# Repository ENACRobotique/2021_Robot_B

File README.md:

# 2021_Robot_B

Code du robot des 1A du club ENAC Robotique pour la coupe de France de Robotique 2021

## Principe de base du robot:

Le robot est divisé en plusieurs parties:
- Carte Raspberry Pi:

Une carte faisant tourner le système d'exploitation Linux, et donc dotée d'une certaine puissance de calcul.
Elle hébergera le programe AI du projet, qui prendra en charge la gestion des actions, les calculs de déplacement (évitement, pathfinding), ainsi que la communication avec des périphériques de haut-niveau et de bas-niveau (par l'intermédiaire du microcontrolleur).

- Microcontrolleur Teensy:

Une carte disposant de moins de puissance de calcul, mais plus apte à controller les périphériques de bas-niveau tel que les moteurs, servomoteurs, encodeurs, etc.
Cette carte devra exécuter les instructions reçues par voie série envoyées par le RPi, et pourra lui envoyer des messages contenant par exemple des informations de positions calculées d'après les mouvements de roues encodeuses.

- Périphériques de haut-niveau:

Dans cette catégorie est par exemple rangé le LIDAR, qui permet d'obtenir des informations sur les objets se trouvant dans l'envrionnement du robot (autres robots en mouvement par exemple), ou un éventuel capteur de distance à ultrasons (si implémenté). Ils sont controllés directement par le RPi.

- Périphérique de bas-niveau:

Dans cette catégorie sont rangés les moteurs, servomoteurs, encodeurs et autres actionneurs nécessitant d'être controllés précisément. Ils sont controllés par le microcontrolleur.

## Structure Logicielle

En raison de la pandémie de Coronavirus, et du confinement, il ne nous est pas possible de travailler en mélangeant phase de conception et phase pratique. Il est donc nécessaire de pouvoir tester certaines parties du programme qui nécéssite des composants physiques, comme les moteurs, capteurs et autres.

Il a donc été décidé de développer des programmes reproduisant le comportement de ces composants physiques, et permettant de tester des algorithmes s'appuyant sur l'environnement physique du robot.

Schéma représentatif de l'architecture logicielle des différents programmes

### Programmes qui seront embarqués sur le robot (/real/)

- ai :

Le programme qui sera hébergé sur le RPi. Ce programme prendra en charge la gestion des actions, les calculs de déplacement (évitement, pathfinding), l'envoi/réception de messages par la voie série avec le microcontrolleur et controller les périphériques de haut-niveau.

- base :

Le programme sera hébergé sur le microcontrolleur.
Il devra gérer l'envoi/réception de messages par la voie série avec le RPi, et controller les différents périphériques de bas-niveau.

(Les dépendances ne sont pas indiquées ici, merci de vous référer aux README de chaque dossier.)

### Programmes destinés à la simulation (/simu/)

- simu/mym.py:

Ce programme a pour but de reproduire le comportement du microcontrolleur, ainsi que des périphériques de bas-niveau qui y seront connectés. Il est possible d'introduire des erreurs factices afin de tester la robustesse du reste du programme.

- simu/hlm.py:

Ce programme a pour but de reproduire le comportement des périphériques de haut-niveau qui seront connectés au RPi (notamment le LIDAR). Ce programme pourra exploiter les données du NVMU (émulateur d'environnement afin de permettre le test d'algorithmes basés sur l'environnement du robot (comme la détection d'obstacles ou le pathfinding)).

- simu/nvmu.py:

Ce programme a pur but de créer un environnement virtuel qui puisse être exploités par les périhpériques de haut-niveau virtuels, en absence de tests physique. Une fidélité physique complète n'est pas le but recherché, le NVMU ne sera qu'en 2D, le but ne'étant que de pouvoir affiner les algorithmes qui seront utilisés sur le vrai robot.

- simu/emulate_serial_ports.sh:

Un script permettant de mettre en place des canaux de communication série virtuels.

### Programme annexe dédié à la visualisation (/visu/)

- visu/visu.py: (nom hypothétique)

Le but de ce programme est d'offrir aux développeurs un moyen de regarder en temps réel ce que l'AI calcule, et si les résultats sont conformes aux attentes. Le programme pourra accéder aux informations calculées par l'AI, et pourra voir ou modifier le NVMU si il est lancé, afin de voir la réaction du robot.

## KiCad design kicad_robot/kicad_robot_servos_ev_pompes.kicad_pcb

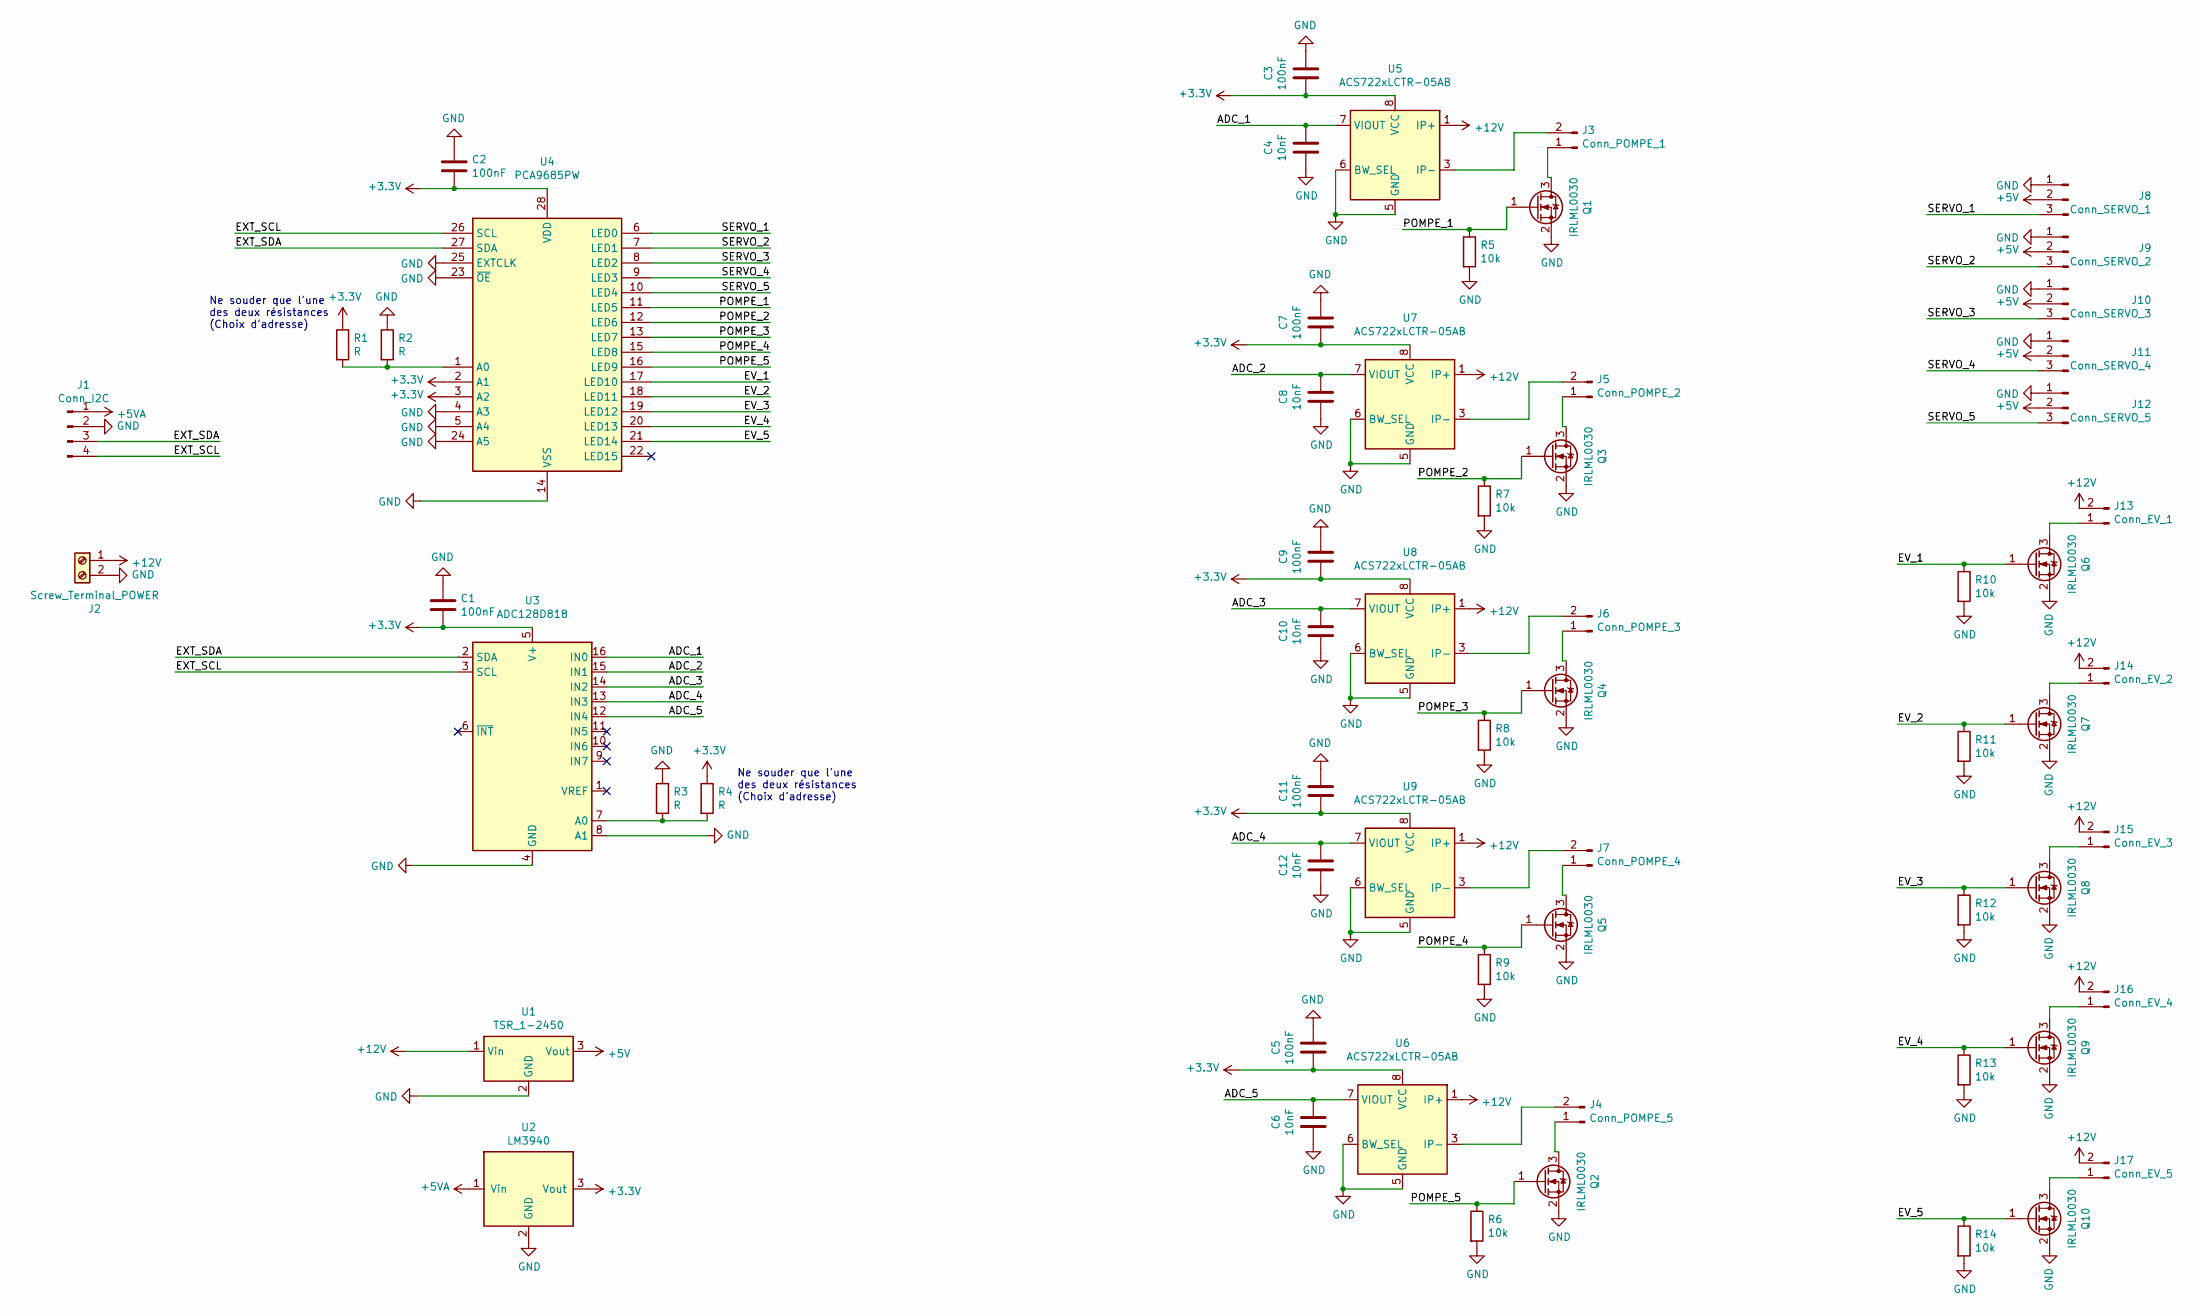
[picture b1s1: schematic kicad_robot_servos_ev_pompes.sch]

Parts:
C1, C2, C3, C5, C7, C9, C11: 100nF; C_0603_1608Metric_Pad1.08x0.95mm_HandSolder
C4, C6, C8, C10, C12: 10nF; C_0603_1608Metric_Pad1.08x0.95mm_HandSolder
J1: Conn_I2C; JST_XH_B4B-XH-A_1x04_P2.50mm_Vertical
J2: Screw_Terminal_POWER; TerminalBlock_bornier-2_P5.08mm
J3: Conn_POMPE_1; JST_XH_B2B-XH-A_1x02_P2.50mm_Vertical
J4: Conn_POMPE_5; JST_XH_B2B-XH-A_1x02_P2.50mm_Vertical
J5: Conn_POMPE_2; JST_XH_B2B-XH-A_1x02_P2.50mm_Vertical
J6: Conn_POMPE_3; JST_XH_B2B-XH-A_1x02_P2.50mm_Vertical
J7: Conn_POMPE_4; JST_XH_B2B-XH-A_1x02_P2.50mm_Vertical
J8: Conn_SERVO_1; PinHeader_1x03_P2.54mm_Vertical
J9: Conn_SERVO_2; PinHeader_1x03_P2.54mm_Vertical
J10: Conn_SERVO_3; PinHeader_1x03_P2.54mm_Vertical
J11: Conn_SERVO_4; PinHeader_1x03_P2.54mm_Vertical
J12: Conn_SERVO_5; PinHeader_1x03_P2.54mm_Vertical
J13: Conn_EV_1; JST_XH_B2B-XH-A_1x02_P2.50mm_Vertical
J14: Conn_EV_2; JST_XH_B2B-XH-A_1x02_P2.50mm_Vertical
J15: Conn_EV_3; JST_XH_B2B-XH-A_1x02_P2.50mm_Vertical
J16: Conn_EV_4; JST_XH_B2B-XH-A_1x02_P2.50mm_Vertical
J17: Conn_EV_5; JST_XH_B2B-XH-A_1x02_P2.50mm_Vertical
Q1, Q2, Q3, Q4, Q5, Q6, Q7, Q8, Q9, Q10: IRLML0030; SOT-23
R1, R2, R3, R4: R; R_0603_1608Metric_Pad0.98x0.95mm_HandSolder
R5, R6, R7, R8, R9, R10, R11, R12, R13, R14: 10k; R_0603_1608Metric_Pad0.98x0.95mm_HandSolder
U1: TSR_1-2450; Converter_DCDC_TRACO_TSR-1_THT
U2: LM3940; SOT-223-3_TabPin2
U3: ADC128D818; TSSOP-16_4.4x5mm_P0.65mm
U4: PCA9685PW; TSSOP-28_4.4x9.7mm_P0.65mm
U5, U6, U7, U8, U9: ACS722xLCTR-05AB; SOIC-8_3.9x4.9mm_P1.27mm

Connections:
+3V3: C1.2, C2.2, C3.2, C5.2, C7.2, C9.2, C11.2, R1.1, R4.1, U2.3 (Vout), U3.5 (V+), U4.2 (A1), U4.3 (A2), U4.28 (VDD), U5.8 (VCC), U6.8 (VCC), U7.8 (VCC), U8.8 (VCC), U9.8 (VCC)
+5V: J8.2, J9.2, J10.2, J11.2, J12.2, U1.3 (Vout)
+5VA: J1.1, U2.1 (Vin)
+12V: J2.1, J13.2, J14.2, J15.2, J16.2, J17.2, U1.1 (Vin), U5.1 (IP+), U5.2 (IP+), U6.1 (IP+), U6.2 (IP+), U7.1 (IP+), U7.2 (IP+), U8.1 (IP+), U8.2 (IP+), U9.1 (IP+), U9.2 (IP+)
/ADC_1: C4.1, U3.16 (IN0), U5.7 (VIOUT)
/ADC_2: C8.1, U3.15 (IN1), U7.7 (VIOUT)
/ADC_3: C10.1, U3.14 (IN2), U8.7 (VIOUT)
/ADC_4: C12.1, U3.13 (IN3), U9.7 (VIOUT)
/ADC_5: C6.1, U3.12 (IN4), U6.7 (VIOUT)
/EV_1: Q6.1 (G), R10.1, U4.17 (LED10)
/EV_2: Q7.1 (G), R11.1, U4.18 (LED11)
/EV_3: Q8.1 (G), R12.1, U4.19 (LED12)
/EV_4: Q9.1 (G), R13.1, U4.20 (LED13)
/EV_5: Q10.1 (G), R14.1, U4.21 (LED14)
/EXT_SCL: J1.4, U3.3 (SCL), U4.26 (SCL)
/EXT_SDA: J1.3, U3.2 (SDA), U4.27 (SDA)
/POMPE_1: Q1.1 (G), R5.1, U4.11 (LED5)
/POMPE_2: Q3.1 (G), R7.1, U4.12 (LED6)
/POMPE_3: Q4.1 (G), R8.1, U4.13 (LED7)
/POMPE_4: Q5.1 (G), R9.1, U4.15 (LED8)
/POMPE_5: Q2.1 (G), R6.1, U4.16 (LED9)
/SERVO_1: J8.3, U4.6 (LED0)
/SERVO_2: J9.3, U4.7 (LED1)
/SERVO_3: J10.3, U4.8 (LED2)
/SERVO_4: J11.3, U4.9 (LED3)
/SERVO_5: J12.3, U4.10 (LED4)
GND: C1.1, C2.1, C3.1, C4.2, C5.1, C6.2, C7.1, C8.2, C9.1, C10.2, C11.1, C12.2, J1.2, J2.2, J8.1, J9.1, J10.1, J11.1, J12.1, Q1.2 (S), Q2.2 (S), Q3.2 (S), Q4.2 (S), Q5.2 (S), Q6.2 (S), Q7.2 (S), Q8.2 (S), Q9.2 (S), Q10.2 (S), R2.1, R3.1, R5.2, R6.2, R7.2, R8.2, R9.2, R10.2, R11.2, R12.2, R13.2, R14.2, U1.2 (GND), U2.2 (GND), U3.4 (GND), U3.8 (A1), U4.4 (A3), U4.5 (A4), U4.14 (VSS), U4.23 (~OE), U4.24 (A5), U4.25 (EXTCLK), U5.5 (GND), U5.6 (BW_SEL), U6.5 (GND), U6.6 (BW_SEL), U7.5 (GND), U7.6 (BW_SEL), U8.5 (GND), U8.6 (BW_SEL), U9.5 (GND), U9.6 (BW_SEL)
unnamed: J3.1, Q1.3 (D)
unnamed: J3.2, U5.3 (IP-), U5.4 (IP-)
unnamed: J4.1, Q2.3 (D)
unnamed: J4.2, U6.3 (IP-), U6.4 (IP-)
unnamed: J5.1, Q3.3 (D)
unnamed: J5.2, U7.3 (IP-), U7.4 (IP-)
unnamed: J6.1, Q4.3 (D)
unnamed: J6.2, U8.3 (IP-), U8.4 (IP-)
unnamed: J7.1, Q5.3 (D)
unnamed: J7.2, U9.3 (IP-), U9.4 (IP-)
unnamed: J13.1, Q6.3 (D)
unnamed: J14.1, Q7.3 (D)
unnamed: J15.1, Q8.3 (D)
unnamed: J16.1, Q9.3 (D)
unnamed: J17.1, Q10.3 (D)
unnamed: R1.2, R2.2, U4.1 (A0)
unnamed: R3.2, R4.2, U3.7 (A0)

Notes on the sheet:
Ne souder que l'une des deux résistances (Choix d'adresse)

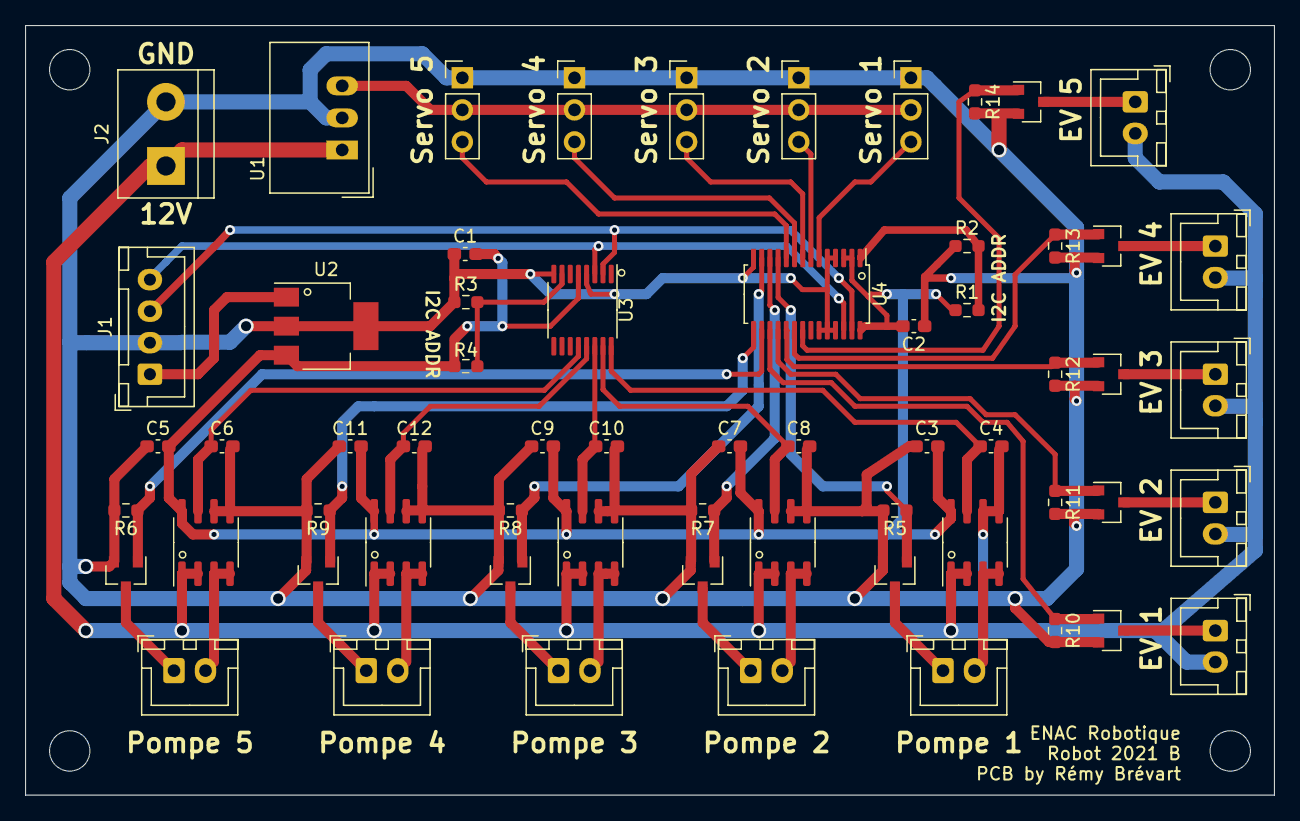
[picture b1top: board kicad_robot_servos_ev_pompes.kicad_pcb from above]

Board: 2 copper layers, 99.0 x 61.0 mm, 62 parts (0 on the bottom side), 44 nets.

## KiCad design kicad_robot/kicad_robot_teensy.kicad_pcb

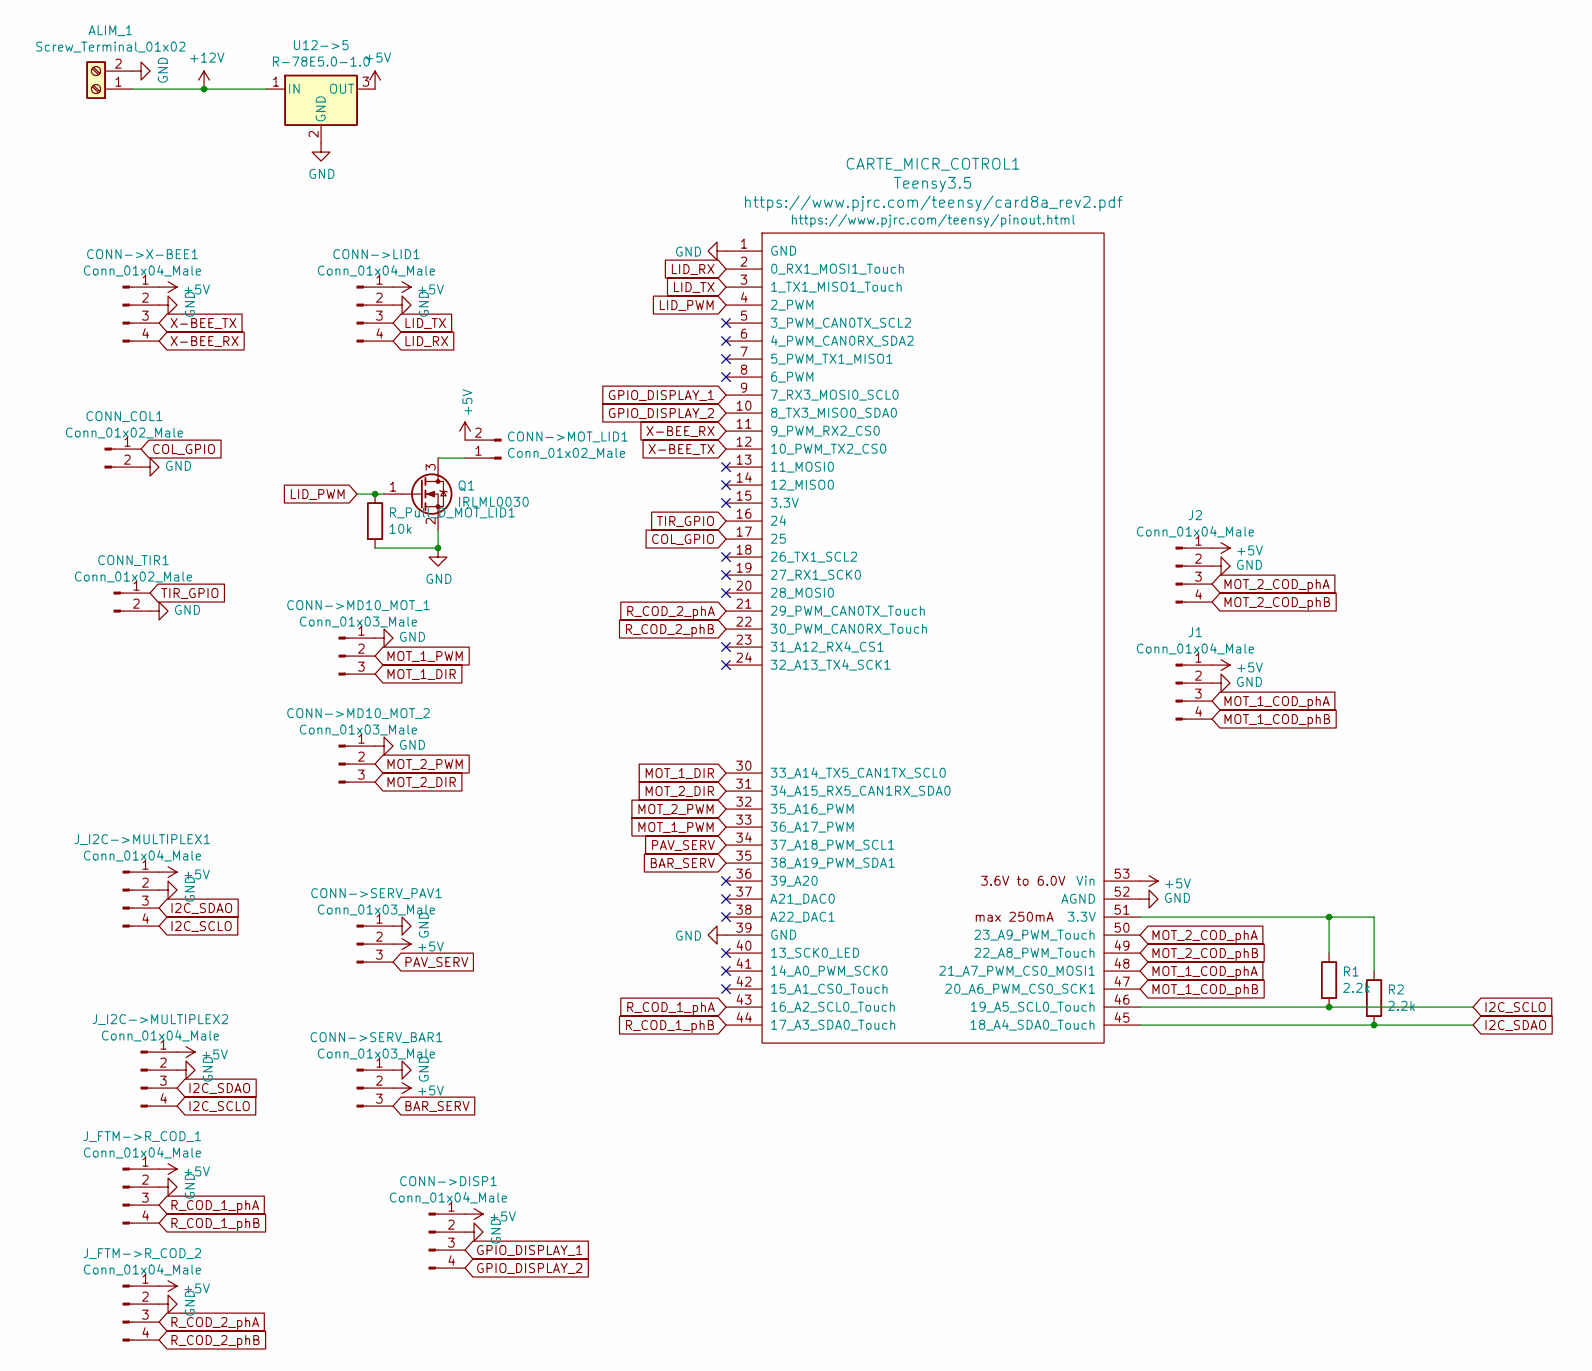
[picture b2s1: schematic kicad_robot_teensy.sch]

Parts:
ALIM_1: Screw_Terminal_01x02; TerminalBlock_bornier-2_P5.08mm
CARTE_MICR_COTROL1: Teensy3.5; Teensy35_36
CONN->DISP1: Conn_01x04_Male; JST_XH_B4B-XH-A_1x04_P2.50mm_Vertical
CONN->LID1: Conn_01x04_Male; JST_XH_B4B-XH-A_1x04_P2.50mm_Vertical
CONN->MD10_MOT_1, CONN->MD10_MOT_2: Conn_01x03_Male; JST_XH_B3B-XH-A_1x03_P2.50mm_Vertical
CONN->MOT_LID1: Conn_01x02_Male; JST_XH_B2B-XH-A_1x02_P2.50mm_Vertical
CONN->SERV_BAR1: Conn_01x03_Male; PinHeader_1x03_P2.54mm_Vertical
CONN->SERV_PAV1: Conn_01x03_Male; PinHeader_1x03_P2.54mm_Vertical
CONN->X-BEE1: Conn_01x04_Male; JST_XH_B4B-XH-A_1x04_P2.50mm_Vertical
CONN_COL1: Conn_01x02_Male; JST_XH_B2B-XH-A_1x02_P2.50mm_Vertical
CONN_TIR1: Conn_01x02_Male; JST_XH_B2B-XH-A_1x02_P2.50mm_Vertical
J1, J2: Conn_01x04_Male
J_FTM->R_COD_1, J_FTM->R_COD_2: Conn_01x04_Male; JST_XH_B4B-XH-A_1x04_P2.50mm_Vertical
J_I2C->MULTIPLEX1, J_I2C->MULTIPLEX2: Conn_01x04_Male; JST_XH_B4B-XH-A_1x04_P2.50mm_Vertical
Q1: IRLML0030; SOT-23
R1, R2: 2.2k; R_0603_1608Metric_Pad0.98x0.95mm_HandSolder
R_Pull_D_MOT_LID1: 10k; R_0603_1608Metric_Pad0.98x0.95mm_HandSolder
U12->5: R-78E5.0-1.0; Converter_DCDC_RECOM_R-78E-0.5_THT

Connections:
+5V: CARTE_MICR_COTROL1.53 (Vin), CONN->DISP1.1, CONN->LID1.1, CONN->MOT_LID1.2, CONN->SERV_BAR1.2, CONN->SERV_PAV1.2, CONN->X-BEE1.1, J1.1, J2.1, J_FTM->R_COD_1.1, J_FTM->R_COD_2.1, J_I2C->MULTIPLEX1.1, J_I2C->MULTIPLEX2.1, U12->5.3 (OUT)
+12V: ALIM_1.1, U12->5.1 (IN)
BAR_SERV: CARTE_MICR_COTROL1.35 (38_A19_PWM_SDA1), CONN->SERV_BAR1.3
COL_GPIO: CARTE_MICR_COTROL1.17 (25), CONN_COL1.1
GND: ALIM_1.2, CARTE_MICR_COTROL1.1 (GND), CARTE_MICR_COTROL1.39 (GND), CARTE_MICR_COTROL1.52 (AGND), CONN->DISP1.2, CONN->LID1.2, CONN->MD10_MOT_1.1, CONN->MD10_MOT_2.1, CONN->SERV_BAR1.1, CONN->SERV_PAV1.1, CONN->X-BEE1.2, CONN_COL1.2, CONN_TIR1.2, J1.2, J2.2, J_FTM->R_COD_1.2, J_FTM->R_COD_2.2, J_I2C->MULTIPLEX1.2, J_I2C->MULTIPLEX2.2, Q1.2 (S), R_Pull_D_MOT_LID1.2, U12->5.2 (GND)
GPIO_DISPLAY_1: CARTE_MICR_COTROL1.9 (7_RX3_MOSI0_SCL0), CONN->DISP1.3
GPIO_DISPLAY_2: CARTE_MICR_COTROL1.10 (8_TX3_MISO0_SDA0), CONN->DISP1.4
I2C_SCLO: CARTE_MICR_COTROL1.46 (19_A5_SCL0_Touch), J_I2C->MULTIPLEX1.4, J_I2C->MULTIPLEX2.4, R1.2
I2C_SDAO: CARTE_MICR_COTROL1.45 (18_A4_SDA0_Touch), J_I2C->MULTIPLEX1.3, J_I2C->MULTIPLEX2.3, R2.2
LID_PWM: CARTE_MICR_COTROL1.4 (2_PWM), Q1.1 (G), R_Pull_D_MOT_LID1.1
LID_RX: CARTE_MICR_COTROL1.2 (0_RX1_MOSI1_Touch), CONN->LID1.4
LID_TX: CARTE_MICR_COTROL1.3 (1_TX1_MISO1_Touch), CONN->LID1.3
MOT_1_COD_phA: CARTE_MICR_COTROL1.48 (21_A7_PWM_CS0_MOSI1), J1.3
MOT_1_COD_phB: CARTE_MICR_COTROL1.47 (20_A6_PWM_CS0_SCK1), J1.4
MOT_1_DIR: CARTE_MICR_COTROL1.30 (33_A14_TX5_CAN1TX_SCL0), CONN->MD10_MOT_1.3
MOT_1_PWM: CARTE_MICR_COTROL1.33 (36_A17_PWM), CONN->MD10_MOT_1.2
MOT_2_COD_phA: CARTE_MICR_COTROL1.50 (23_A9_PWM_Touch), J2.3
MOT_2_COD_phB: CARTE_MICR_COTROL1.49 (22_A8_PWM_Touch), J2.4
MOT_2_DIR: CARTE_MICR_COTROL1.31 (34_A15_RX5_CAN1RX_SDA0), CONN->MD10_MOT_2.3
MOT_2_PWM: CARTE_MICR_COTROL1.32 (35_A16_PWM), CONN->MD10_MOT_2.2
unnamed: CARTE_MICR_COTROL1.51 (3.3V), R1.1, R2.1
unnamed: CONN->MOT_LID1.1, Q1.3 (D)
PAV_SERV: CARTE_MICR_COTROL1.34 (37_A18_PWM_SCL1), CONN->SERV_PAV1.3
R_COD_1_phA: CARTE_MICR_COTROL1.43 (16_A2_SCL0_Touch), J_FTM->R_COD_1.3
R_COD_1_phB: CARTE_MICR_COTROL1.44 (17_A3_SDA0_Touch), J_FTM->R_COD_1.4
R_COD_2_phA: CARTE_MICR_COTROL1.21 (29_PWM_CAN0TX_Touch), J_FTM->R_COD_2.3
R_COD_2_phB: CARTE_MICR_COTROL1.22 (30_PWM_CAN0RX_Touch), J_FTM->R_COD_2.4
TIR_GPIO: CARTE_MICR_COTROL1.16 (24), CONN_TIR1.1
X-BEE_RX: CARTE_MICR_COTROL1.11 (9_PWM_RX2_CS0), CONN->X-BEE1.4
X-BEE_TX: CARTE_MICR_COTROL1.12 (10_PWM_TX2_CS0), CONN->X-BEE1.3

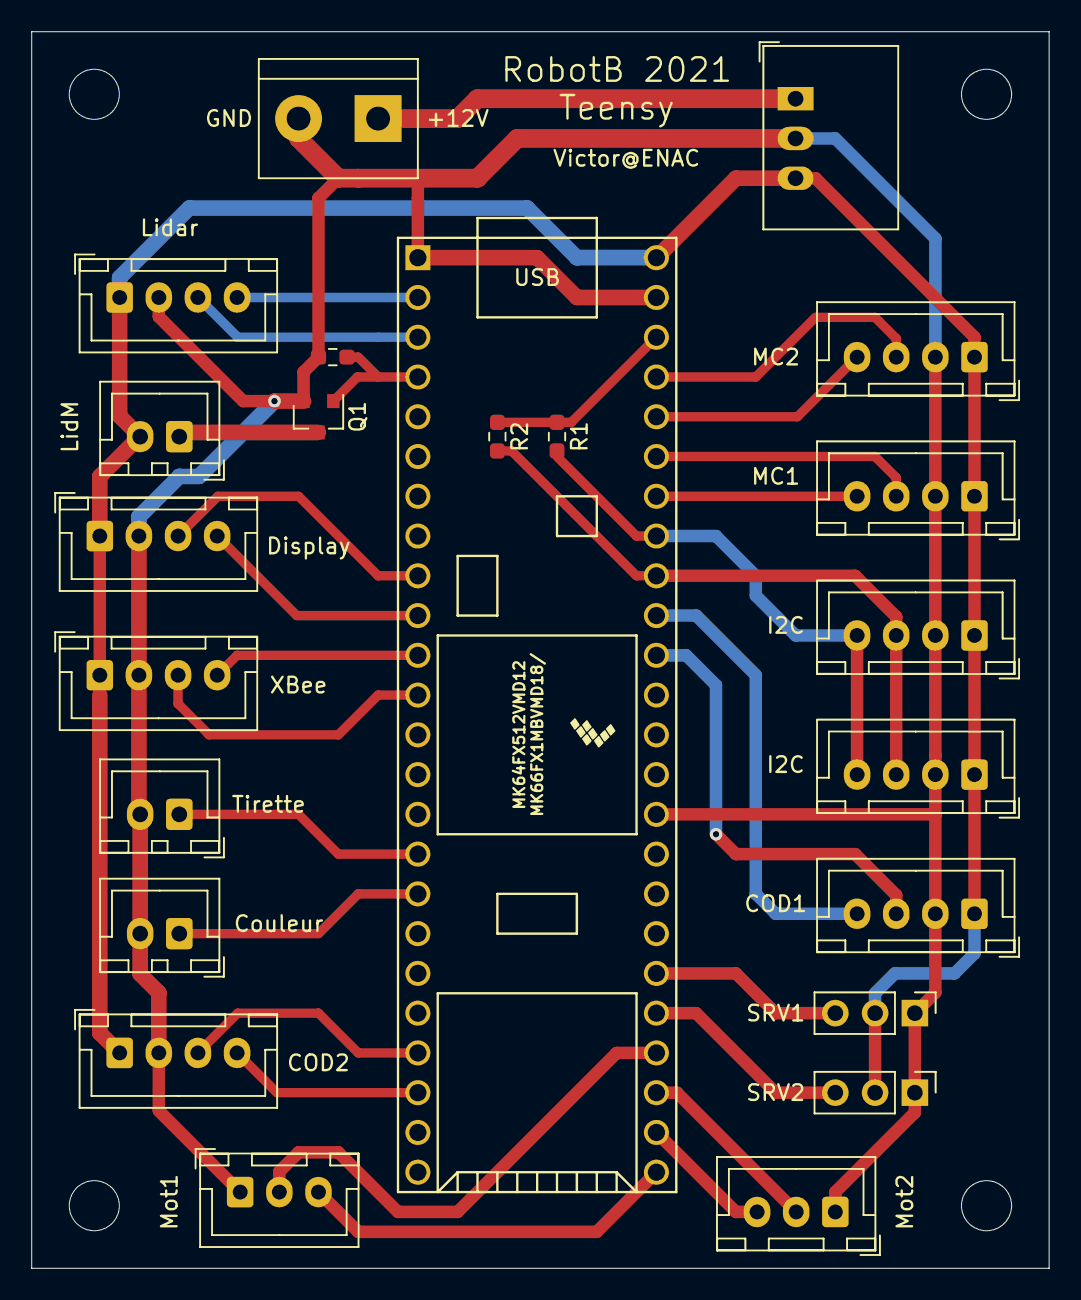
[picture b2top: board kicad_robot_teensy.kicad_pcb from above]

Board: 2 copper layers, 65.0 x 79.0 mm, 23 parts (0 on the bottom side), 30 nets.

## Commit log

2020-11-08 Adds structure for simulator and AI development.
2020-11-08 Quelques changements mineurs pour satisfaire Pylint
2020-11-08 Petits correctifs pour satisfaire Pylint
2020-11-09 Description d'une possible l'architecture du projet modification de la hiérarchie du code pour refléter cette architecture
2020-11-09 (ajout d'un saut de ligne)
2020-11-09 (petite correction)
2020-11-16 Adds communication lib and update examples.
2020-11-16 Adds template teensy project with basic communication.
2021-02-01 Cleanup du repo
2021-02-11 Ajout du répertoire du projet kicad
2021-02-11 KiCAD
2021-02-15 Avancement sur la carte
2021-02-20 Ajout Petite Carte
2021-02-22 Petit avancement
2021-02-22 ajout des copies des librairies teensy utilisées
2021-02-22 Renommage
2021-02-22 del gitignore
2021-02-22 del ignore libs and restore other gitignore
2021-02-22 mise à jour
2021-02-22 Séparation de l'alimentation du LM3940
2021-02-22 Modif mineure LM3940 (épaisseur trait)
2021-02-22 Reversed some connectors
2021-02-22 Capa de découplage PCA
2021-02-22 Ajout des derniers composants
2021-02-22 Footprint attribution
2021-02-22 Created netlist and imported in pcb
2021-02-22 Ajout des footprint carte teensy
2021-02-23 Finalisation du fichier SCH/ Début fichier PCB
2021-02-24 Routage de la carte Teensy V1.0
2021-02-25 Placement des composants
2021-02-25 Réarrangement des composants / Routage (v1)
2021-02-25 Ajout de sérigraphie pour repérer les numéros d'équipements facilement sur la carte
2021-03-04 Carte Teensy V2.0
2021-03-04 Routage V2 de la carte servos/ev/pompes
2021-03-11 copie code des 2A
2021-03-11 code pour tester le roulage du robot
2021-03-11 Routage Carte Servos/EV/Pompes v3 (avec mounting holes)
2021-03-11 Déplacement de quelques labels (changement mineur)
2021-03-13 params update
2021-03-13 update xbee
2021-03-13 Calage des edge cuts et des mounting holes sur grille 1mm, épaissisement et décalage tracks
2021-03-13 Écartement de vias et pistes encore trop proches
2021-03-14 Passage de certaines tracks en bottom, supression de vias inutiles
2021-03-14 Support pins (mais non logiciel) de 4 encodeurs
2021-03-15 update pins
2021-03-15 Agrandissement des vias (source des mosfets, GND des résistances EV), cache des REF**
2021-03-15 debut code recalibration
2021-03-15 commentaire pour navgator.cpp
2021-03-16 ajout code lidar 2019
2021-03-16 Cache de labels inutiles
2021-03-16 Teensy V2.1: Carte presque prête
2021-03-18 update asservissement
2021-03-25 Carte Tennsy version finale
2021-03-25 Génération Gerber Carte Servos
2021-03-25 Ignore les zips de gerber_servos et gerber_teensy
2021-03-25 copie des fichiers du repo secondaire/2019 pour modification
2021-03-25 moving folder
2021-03-25 Moved lidar tests to another projects in separate workspace
2021-03-25 code basique pour essayer de récupérer les données du lidar
2021-03-25 des tests
2021-03-26 Changement vers teensy 3.5, essais
2021-03-31 added fsmSupervisor, starting to think about pathfinding
2021-03-31 first statemachine
2021-03-31 added deploy with "d"
2021-04-03 added utils
2021-04-03 update abstract state
2021-04-03 test fsm state
2021-04-03 ajout abstract state servo
2021-04-03 abstract state, regroupement des Serial dans params.h
2021-04-03 update serial
2021-04-03 beggining recalibration code Better abstract state
2021-04-03 moved recalibration in utils
2021-04-03 move closest wall coordinate to utils
2021-04-05 releaseFrontServo copy and pase
2021-04-05 abstract state advances
2021-04-07 update pompe
2021-04-14 params nouvelle carte
2021-04-15 WIP sur InterfaceLidar
2021-04-15 add comments
2021-04-16 test commit
2021-04-22 wip lidar
2021-04-22 Le code compile (mise en commentaire)
2021-04-28 mise a jour moteur
2021-04-30 copy paste trajcetory
2021-05-03 repassage 2 encodeurs moteur et IHM
2021-05-03 Ajout code action, pseudo code matchDirector
2021-05-03 flowchart ajout
2021-05-03 commentaire match director
2021-05-03 Ajout passage absolue - relatif
2021-05-04 modif mineure sur conditions
2021-05-08 maj du match director pour calcul tps + refactor abstract
2021-05-08 removed uselss dependency, moved code to secondary
2021-05-09 Moved ai inside src
2021-05-12 commit jsp quoi
2021-05-12 update params
2021-05-12 ajout de pins manquant
2021-05-12 Début code attrape gobelet
2021-05-13 avancement actuator
2021-05-13 solved merge problem params.h
2021-05-13 micro update
2021-05-13 Refactorisation pour state movement arm
2021-05-13 initiate mvt paradigm - one class per state
2021-05-13 refactorisation de MoveServo
2021-05-18 Code pavillon ajouté
2021-05-19 added library & test code
2021-05-19 region adedd
2021-05-19 code de test basique PCA8596
2021-05-20 update adrr
2021-05-21 ajout code ctrl servo PCA
2021-05-24 modifs du jeudi 20 mai (bcp de bugs, et pas bcp de progrès)
2021-05-24 Ajout d'un code de test de recallibration
2021-05-25 update motor
2021-05-25 ajout test serial
2021-05-25 recalibration enfaite pas besoin de timer, géré ds fsm
2021-05-26 updateMotorControl
2021-05-27 ajout code test matchdirector pavillon
2021-05-27 small params change
2021-05-27 wheelbase coder
2021-05-27 params
2021-05-28 update time calculation, beginning to transition odometry to class
2021-05-31 mise à jour odométrie, test matchdirector
2021-06-01 Probléme pour fsmSupervisor -> bloque Probléme pour pwmServo : pins fréquence
2021-06-02 mise a jour test
2021-06-02 pwm ev working
2021-06-02 PCA fonctionnel
2021-06-04 Code fonctionnel PCA, moitié match director - avant mise à jour odométrie
2021-06-04 modifs mineures, IHM non reliée
2021-06-04 moved utils - version finale avant refactorisation odmetry
2021-06-05 Test odométrie
2021-06-06 code pour tester recalibration via 'r' en comm.h
2021-06-06 odometry qui déconne
2021-06-06 modification pour capter des messages de l'IHM
2021-06-06 Ajout de la bibliothèque du display
2021-06-06 del lidar test worskapce qui aurait dû être dans sa propre branche
2021-06-06 added lidar libs and pathfinding (empty) files
2021-06-07 test odo part 2 non fonctionnel
2021-06-07 update odometry ne marche pas
2021-06-08 update secondary
2021-06-08 still investigating
2021-06-08 recalibration wall done, removed some warning
2021-06-08 wip pathfinding & del lid libs since xv11 is ded (repose en paix petit ange parti trop tôt)
2021-06-09 update odometry & platforio
2021-06-09 rajout de nom en haut de certains fichiers, modif matchdirector car bug changement d'état
2021-06-09 ajout de "droit d'auteur"
2021-06-09 wip pathfinding
2021-06-10 Test recalibration
2021-06-10 bugfix
2021-06-10 bruh
2021-06-10 tries to use deepcopy
2021-06-10 Ajout de code pour un display. (Non testé, et non actif)
2021-06-10 Ajout du code pour le display (non testé, G pas de compilateur...)
2021-06-10 updat abs to coord correct, update comm pour tests
2021-06-11 gestion score & gestion supp dans match director
2021-06-11 ajout d'état
2021-06-11 fixed bug in header include once, removed warning
2021-06-12 Ajout tentative de recalage roue libre + doc
2021-06-12 Dépendnace inutile retiré
2021-06-13 ajout code (non testé) info girouette parking
2021-06-14 maj valeurs actions & recalibration
2021-06-14 test matchDirector, mise à jour d'actions
2021-06-14 change
2021-06-14 Avancée gestion match action
2021-06-14 Ajout de flags pour la gestion des sections
2021-06-14 proto test runtime sur pc
2021-06-15 debug runtime pathfinding
2021-06-15 restore graph copy
2021-06-15 route table des wp de la coupe (version actuelle)
2021-06-15 some fixes (not tested)
2021-06-15 recompiled pc test / added some deps to secondary2021
2021-06-17 correction x y
2021-06-17 update merge
2021-06-17 added function read_route
2021-06-17 update pathfinding
2021-06-17 updated pc_main + dumped_garbage
2021-06-17 ajout libs RPLidar from github
2021-06-17 update matchDirector
2021-06-17 Code de magie noire - le direction absolue a un pb
2021-06-17 ajout reajustement
2021-06-18 update action list correction overflow d'actionList
2021-06-18 Match director solved merge issue reajustement
2021-06-18 commit buggé
2021-06-22 added actions
2021-06-22 Refactorisation Display Controller - CODE NE COMPILE PAS
2021-06-25 debug msg modif
2021-06-25 update action liste phare + ecocup haut
2021-06-25 action list cleanup
2021-06-25 DisplayController fix compilation
2021-06-25 update ordre des actions
2021-06-25 overshoot navigator
2021-06-25 Revert "update ordre des actions"
    This reverts commit 3a05333fefa9e19189f798e52141dea683b1ef77.
2021-06-25 Revert "action list cleanup"
    This reverts commit 03e076776f8e7dd37833d74504e248ad7a67cdd5.
2021-06-25 Revert "debug msg modif"
    This reverts commit 863c26a380bf812e3a5c07d71da03b3d0babc600.
2021-06-25 added
2021-06-28 updated code actions
2021-06-28 display added
2021-06-28 added tcs
2021-06-29 added check for obstruction between start and first wp as well as last wp and end. added direct route if start and end close enough
2021-06-29 création du conteneur des données lidar, implémentation et quelques modifs. aucun test effectué
2021-06-29 wip take quality of measure into account
2021-06-29 secondary return to nominal with PCA
2021-06-30 test lidar 1
2021-07-01 updated action list
2021-07-01 update major logic
2021-07-01 arrondi de l'angle au plus proche
2021-07-01 updated actionlist
2021-07-02 updating high level code
2021-07-02 updated matchdirector
2021-07-02 pahtfinding added
2021-07-02 final merging
2021-07-03 commit chelou
2021-07-03 prints startbit
2021-07-03 pathfinding disabled
2021-07-03 updated lidar data
2021-07-03 Rplidar qui marche pas
2021-07-03 rp lidar qui est en cours
2021-07-03 commit qui marche pas
2021-07-03 lidarv2 qui marche pas
2021-07-03 livarV2 qui marche pas
2021-07-03 without lidar
2021-07-03 updated params
2021-07-03 pathfinding update
2021-07-03 updt wp pos
2021-07-03 updt wp
2021-07-03 match director update
2021-07-03 pathfinding updated not working
2021-07-03 lidar update
2021-07-03 gufcjbf
2021-07-04 première ébauche de code pour le côté jaune
2021-07-04 lidar updated
2021-07-04 lidar ok?
2021-07-04 adde
2021-07-04 params roue codeuse frottement ajustement
2021-07-04 pathfinding test
2021-07-04 coords updated
2021-07-05 added prints to is_path_is_blocked
2021-07-05 added proximity_check
2021-07-05 added platform limit check
2021-07-05 added SerialCtrl prints
2021-07-05 coordonnées victor, ça marche bien
2021-07-05 Debut de modif pour retirer le pathfinding
2021-07-05 better prints
2021-07-05 update path
2021-07-05 restored time acquisition for LidarData and added check in proximity_check + larger threshold in front of robot
2021-07-05 extended to back of robot
2021-07-05 better print
2021-07-05 commit update
2021-07-05 changed default value and reflected that in proximity_check
2021-07-05 updated yellow side
2021-07-05 update coordonnes droite
2021-07-05 updt seuil inf à 150mm
2021-07-05 update ActionList
2021-07-05 just exclude zero
2021-07-05 added some float comps
2021-07-05 moved prints around
2021-07-05 update recalibration partie jaune
2021-07-05 save
2021-07-06 TRÈS GROS COMMIT
2021-07-06 phare 100%
2021-07-06 ça fonctionne
2021-07-06 code retour
2021-07-06 commit action right updated
2021-07-06 MAJ de dernière minute (bon courage pour la coupe (-: )
2021-07-07 coupe fin premier jour sur place
2021-07-08 angles detect élargis
2021-07-08 Revert "angles detect élargis"
    This reverts commit c3ccdb6df355a3902a5b1103dfec8c89083ffcc5.
2021-07-08 robot stopped modif
2021-07-08 last minute modif remy ver
2021-07-08 pusing actionlsit
2021-07-08 push fix
2021-07-08 rplidar off
2021-07-08 stonks
2021-07-08 del comments
2021-07-08 update phare position
2021-07-08 commit before fucking up right
2021-07-08 push urgent
2021-07-08 push stop urgent
2021-07-08 freinage d'urgence -oirage match 2
2021-07-08 CODE A TESTER
2021-07-09 avant chgm roue codeuse
2021-07-09 commit update roue codeuse
2021-07-09 code série 5
2021-07-09 useless set state removed
2021-07-10 code série 6 - final
2021-07-10 readme update
2021-09-03 Fin Intégration IHM // Suppression de fonctions de communication
